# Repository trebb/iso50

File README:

ISO50 -- a 50% DIY computer keyboard

There are two variants of the ISO50 keyboard: hand-wired and
PCB-based.  Files and directories that have "pcb" in their name are
part of the PCB-based variant.

The hardware part is covered in directory ./hardware.

Firmware is based on TMK (https://github.com/tmk/tmk_keyboard); see
directories ./firmware or ./firmware-pcb, respectively.

http://imgur.com/a/XgsYZ
http://imgur.com/a/m9RCg

The name of this project refers to the standard 105-key ISO keyboard
layout, reduced to 50 %.  It is not related to anything using the
photography-related connotation of the name.  It is not affiliated
with http://blog.iso50.com/.

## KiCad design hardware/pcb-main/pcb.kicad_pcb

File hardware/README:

To build the keyboard, two laser-cut plates, an optional PCB, a
3D-printed frame, and a sticker that covers the screw heads and holes
on the bottom need to be made.

Files in this directory

- top-plate.dxf, bottom-plate.dxf, top-plate-pcb.dxf,
  bottom-plate-pcb.dxf

Files for laser cutting the plates.  Top should be 1.5 mm, bottom
1.0 mm (hand-wired) or 1.5 mm (PCB).

- top-plate-pcb-pcb.dxf

Helper file used for the KiCad project in ./pcb-top-plate/.

- frame.dxf, frame-pcb.dxf

Various shapes and parameters that are read by frame.scad or
frame-pcb.scad, respectively.  frame.dxf also contains a wiring
schema.

- frame.scad, frame-pcb.scad

Renders the (merely decorative) keyboard frame. 'make frame.stl' or
'make frame-pcb.stl' should create a 3D-printable .stl file.

- bottom-label-de.svg, bottom-label-pcb-de.svg

Legend image intended to be put onto the bottom of the keyboard.  'make
bottom-label-de.pdf' or 'make bottom-label-pcb-de.pdf' should create a
printable pdf that can be scaled to A4 size and printed on adhesive
film.

- foot-template.dxf

Template for cutting the bottom label, placing the adhesive feet, and
cutting an insulating layer that goes on top of the bottom plate.

- pcb-main/

KiCad project of the PCB.

- ./pcb-top-plate/, ./pcb-bottom-plate/

KiCad projects containing PCB-shaped alternatives to top-plate-pcb.dxf
and bottom-plate-dxf.

Software used

LibreCAD 2.08 (.dxf)
OpenSCAD 2015.03 (.stl)
Inkscape 0.9.1 (.svg)
KiCad r6904

Other parts:

- 52 Cherry-style switches

- 1 2u Costar stabilizer set

- USB cable: Mini for the hand-wiring, Micro for the PCB.

- An ISO keycap set that contains

  - 6 1.25u bottom row keys (most sets contain 7),

  - 7 1.5u bottom row keys (only a few keysets on the market contain
    that much), and

  - an asymmetrical, stepped CapsLock key

- 12 standoffs M2 x 6.3 mm (hand-wired) or M2 x 4.5 mm (PCB)

- 52 diodes 1N4148

- For the hand wiring:

  - Teensy 2.0

  - 3 LEDs, 3 resistors 330 Ohm

- For components of the PCB variant, consult the KiCad project in
  directory ./pcb-main.

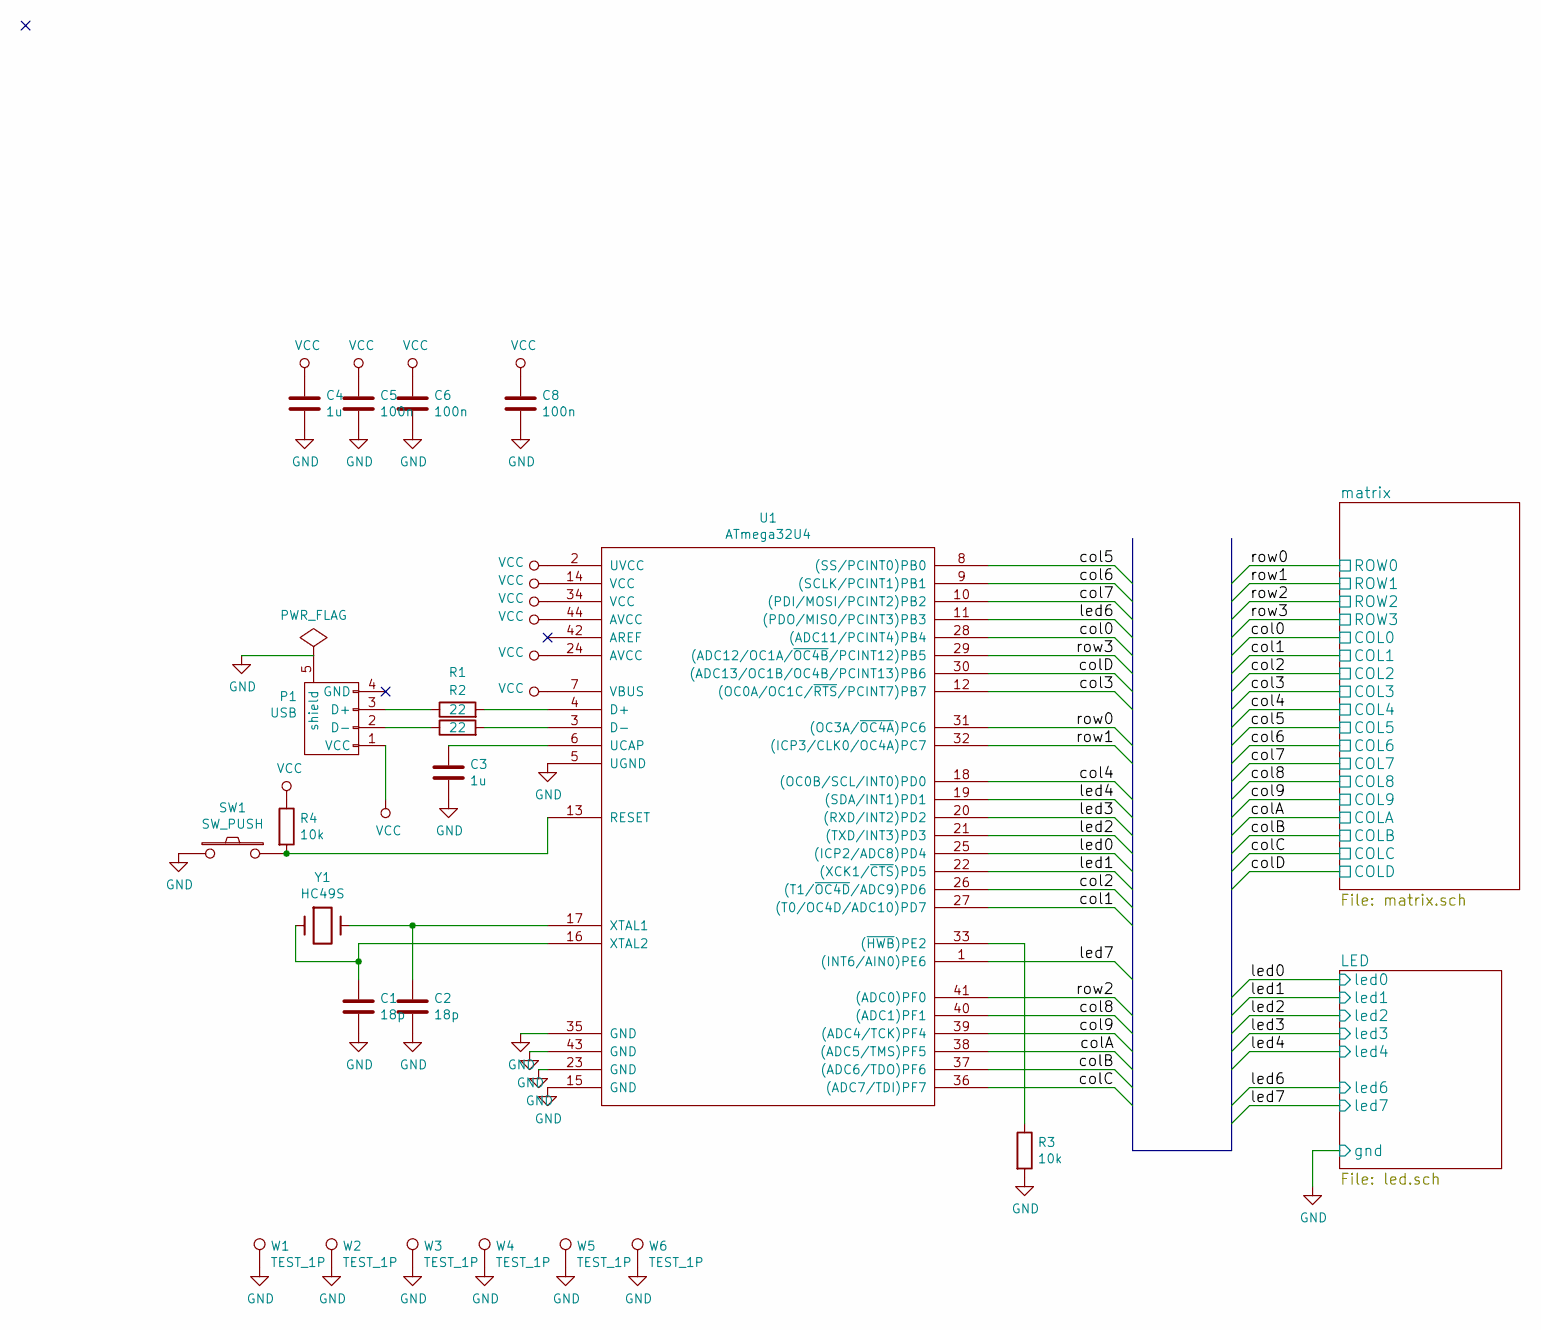
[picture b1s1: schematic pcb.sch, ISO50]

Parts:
C1, C2: 18p; C_1206_HandSoldering
C3, C4: 1u; C_1206_HandSoldering
C5, C6, C8: 100n; C_1206_HandSoldering
P1: USB; USB_Micro-207A-BBA0-R
R1, R2: 22; Resistor_Horizontal_RM7mm
R3, R4: 10k; Resistor_Horizontal_RM7mm
SW1: SW_PUSH; SW_PUSH_SMALL
U1: ATmega32U4; MLF-44_Atmel
W1, W2, W3, W4, W5, W6: TEST_1P; Spring-Contact_SMD
Y1: HC49S; Crystal_HC49-U_Vertical

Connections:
/col0: U1.28 ((ADC11/PCINT4)PB4); also elsewhere on the board
/col1: U1.27 ((T0/OC4D/ADC10)PD7); also elsewhere on the board
/col2: U1.26 ((T1/~OC4D~/ADC9)PD6); also elsewhere on the board
/col3: U1.12 ((OC0A/OC1C/~RTS~/PCINT7)PB7); also elsewhere on the board
/col4: U1.18 ((OC0B/SCL/INT0)PD0); also elsewhere on the board
/col5: U1.8 ((SS/PCINT0)PB0); also elsewhere on the board
/col6: U1.9 ((SCLK/PCINT1)PB1); also elsewhere on the board
/col7: U1.10 ((PDI/MOSI/PCINT2)PB2); also elsewhere on the board
/col8: U1.40 ((ADC1)PF1); also elsewhere on the board
/col9: U1.39 ((ADC4/TCK)PF4); also elsewhere on the board
/colA: U1.38 ((ADC5/TMS)PF5); also elsewhere on the board
/colB: U1.37 ((ADC6/TDO)PF6); also elsewhere on the board
/colC: U1.36 ((ADC7/TDI)PF7); also elsewhere on the board
/colD: U1.30 ((ADC13/OC1B/OC4B/PCINT13)PB6); also elsewhere on the board
/led0: U1.25 ((ICP2/ADC8)PD4); also elsewhere on the board
/led1: U1.22 ((XCK1/~CTS~)PD5); also elsewhere on the board
/led2: U1.21 ((TXD/INT3)PD3); also elsewhere on the board
/led3: U1.20 ((RXD/INT2)PD2); also elsewhere on the board
/led4: U1.19 ((SDA/INT1)PD1); also elsewhere on the board
/led6: U1.11 ((PDO/MISO/PCINT3)PB3); also elsewhere on the board
/led7: U1.1 ((INT6/AIN0)PE6); also elsewhere on the board
/row0: U1.31 ((OC3A/~OC4A~)PC6); also elsewhere on the board
/row1: U1.32 ((ICP3/CLK0/OC4A)PC7); also elsewhere on the board
/row2: U1.41 ((ADC0)PF0); also elsewhere on the board
/row3: U1.29 ((ADC12/OC1A/~OC4B~/PCINT12)PB5); also elsewhere on the board
GND: C1.2, C2.2, C3.2, C4.2, C5.2, C6.2, C8.2, P1.5 (shield), R3.2, SW1.2, U1.5 (UGND), U1.15 (GND), U1.23 (GND), U1.35 (GND), U1.43 (GND), W1.1, W2.1, W3.1, W4.1, W5.1, W6.1; also elsewhere on the board
unnamed: C1.1, U1.16 (XTAL2), Y1.1
unnamed: C2.1, U1.17 (XTAL1), Y1.2
unnamed: C3.1, U1.6 (UCAP)
unnamed: P1.2 (D-), R2.1
unnamed: P1.3 (D+), R1.1
unnamed: R1.2, U1.4 (D+)
unnamed: R2.2, U1.3 (D-)
unnamed: R3.1, U1.33 ((~HWB~)PE2)
unnamed: R4.2, SW1.1, U1.13 (RESET)
VCC: C4.1, C5.1, C6.1, C8.1, P1.1 (VCC), R4.1, U1.2 (UVCC), U1.7 (VBUS), U1.14 (VCC), U1.24 (AVCC), U1.34 (VCC), U1.44 (AVCC)

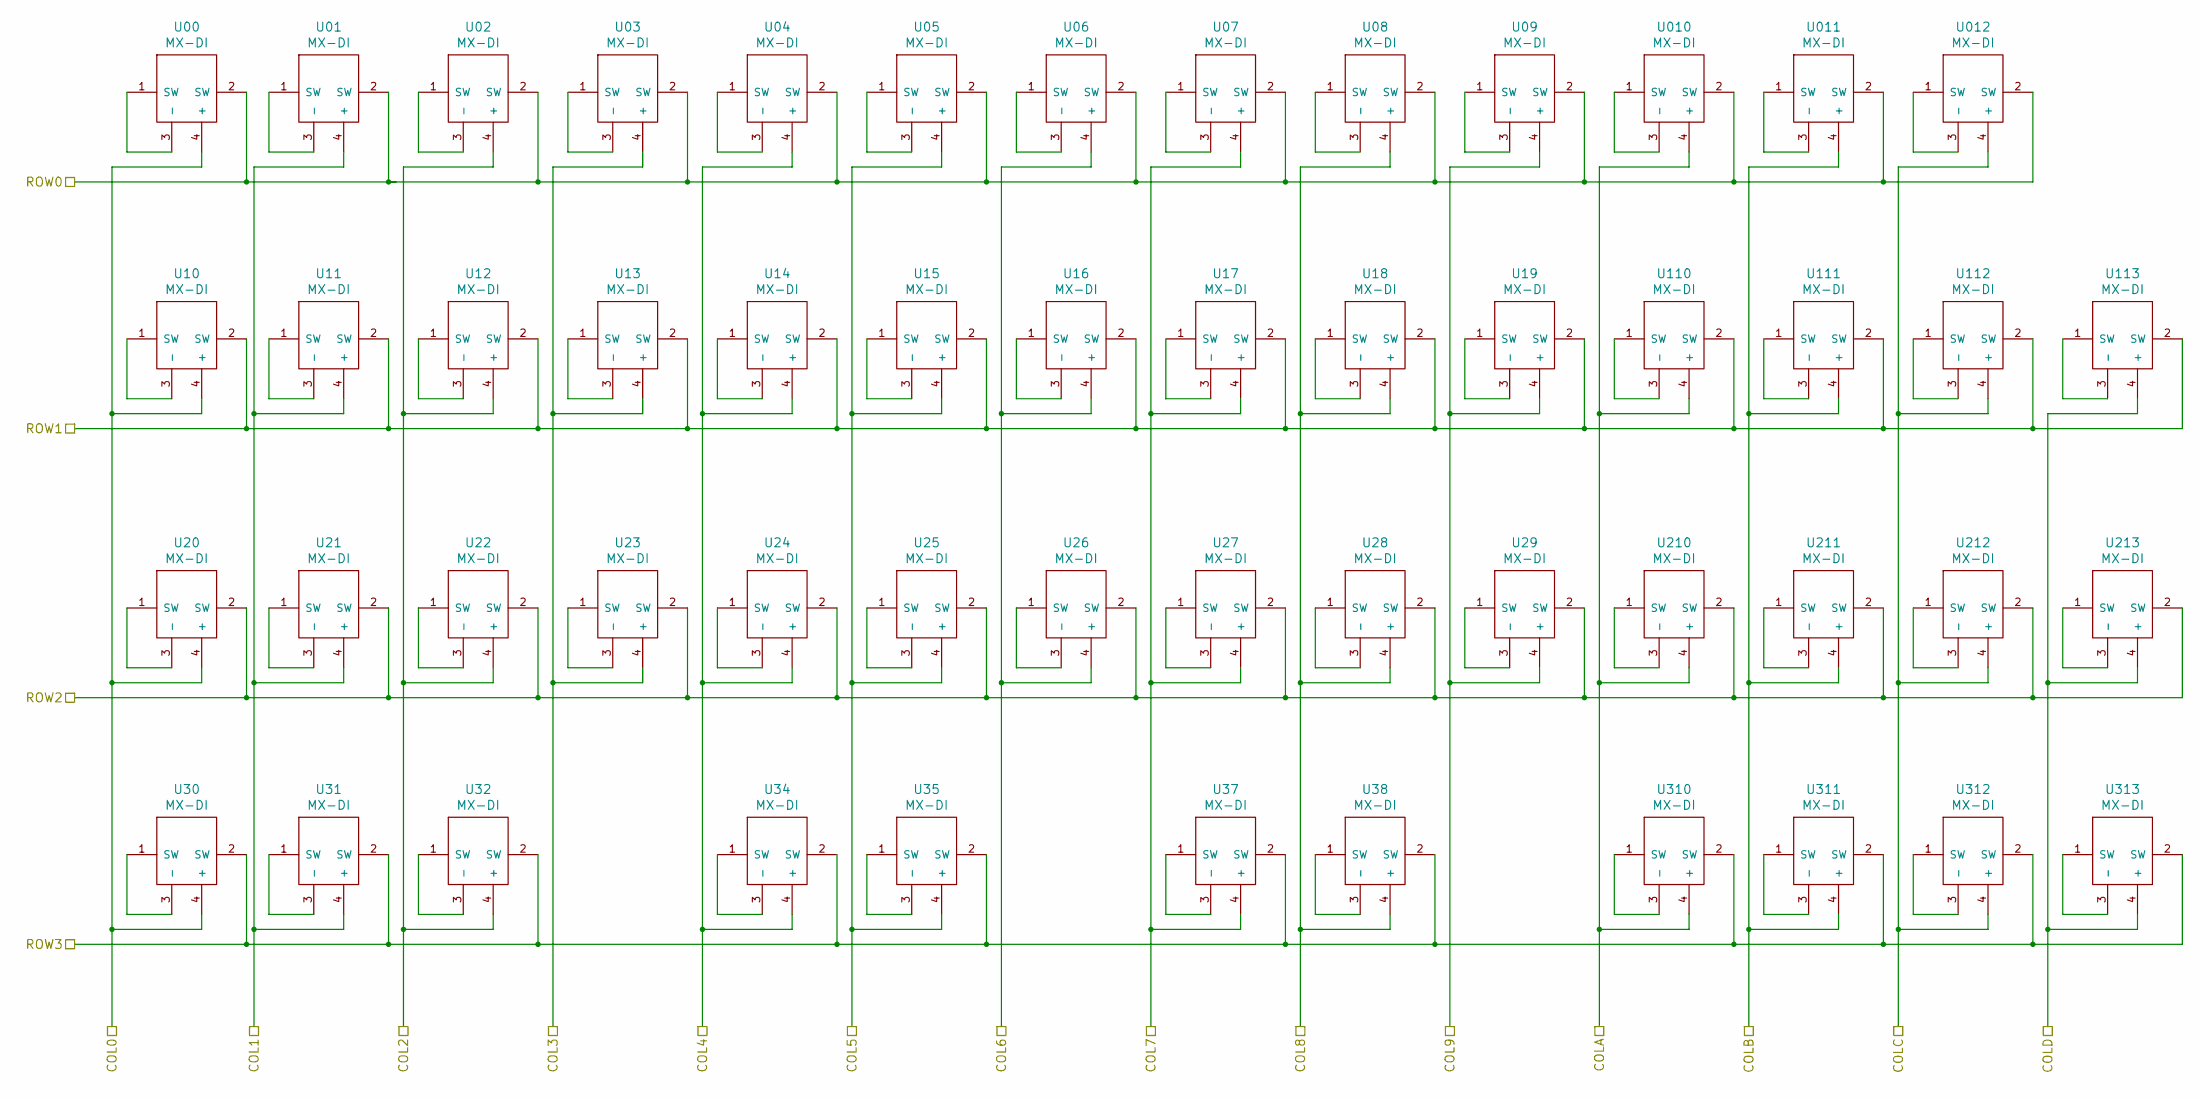
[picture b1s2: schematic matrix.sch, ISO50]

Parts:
U00, U01, U02, U03, U04, U05, U06, U07, U08, U09, U010, U10, U011, U11, U012, U12, U13, U14, U15, U16, U17, U18, U19, U20, U21, U22, U23, U24, U25, U26, U27, U28, U29, U30, U31, U32, U34, U35, U37, U38, U110, U111, U112, U113, U210, U211, U212, U213, U310, U311, U312, U313: MX-DI; MXDIODE

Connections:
/col0: U00.4 (+), U10.4 (+), U20.4 (+), U30.4 (+); also elsewhere on the board
/col1: U01.4 (+), U11.4 (+), U21.4 (+), U31.4 (+); also elsewhere on the board
/col2: U02.4 (+), U12.4 (+), U22.4 (+), U32.4 (+); also elsewhere on the board
/col3: U03.4 (+), U13.4 (+), U23.4 (+); also elsewhere on the board
/col4: U04.4 (+), U14.4 (+), U24.4 (+), U34.4 (+); also elsewhere on the board
/col5: U05.4 (+), U15.4 (+), U25.4 (+), U35.4 (+); also elsewhere on the board
/col6: U06.4 (+), U16.4 (+), U26.4 (+); also elsewhere on the board
/col7: U07.4 (+), U17.4 (+), U27.4 (+), U37.4 (+); also elsewhere on the board
/col8: U08.4 (+), U18.4 (+), U28.4 (+), U38.4 (+); also elsewhere on the board
/col9: U09.4 (+), U19.4 (+), U29.4 (+); also elsewhere on the board
/colA: U010.4 (+), U110.4 (+), U210.4 (+), U310.4 (+); also elsewhere on the board
/colB: U011.4 (+), U111.4 (+), U211.4 (+), U311.4 (+); also elsewhere on the board
/colC: U012.4 (+), U112.4 (+), U212.4 (+), U312.4 (+); also elsewhere on the board
/colD: U113.4 (+), U213.4 (+), U313.4 (+); also elsewhere on the board
/row0: U00.2 (SW), U01.2 (SW), U02.2 (SW), U03.2 (SW), U04.2 (SW), U05.2 (SW), U06.2 (SW), U07.2 (SW), U08.2 (SW), U09.2 (SW), U010.2 (SW), U011.2 (SW), U012.2 (SW); also elsewhere on the board
/row1: U10.2 (SW), U11.2 (SW), U12.2 (SW), U13.2 (SW), U14.2 (SW), U15.2 (SW), U16.2 (SW), U17.2 (SW), U18.2 (SW), U19.2 (SW), U110.2 (SW), U111.2 (SW), U112.2 (SW), U113.2 (SW); also elsewhere on the board
/row2: U20.2 (SW), U21.2 (SW), U22.2 (SW), U23.2 (SW), U24.2 (SW), U25.2 (SW), U26.2 (SW), U27.2 (SW), U28.2 (SW), U29.2 (SW), U210.2 (SW), U211.2 (SW), U212.2 (SW), U213.2 (SW); also elsewhere on the board
/row3: U30.2 (SW), U31.2 (SW), U32.2 (SW), U34.2 (SW), U35.2 (SW), U37.2 (SW), U38.2 (SW), U310.2 (SW), U311.2 (SW), U312.2 (SW), U313.2 (SW); also elsewhere on the board
unnamed: U00.1 (SW), U00.3 (-)
unnamed: U01.1 (SW), U01.3 (-)
unnamed: U02.1 (SW), U02.3 (-)
unnamed: U03.1 (SW), U03.3 (-)
unnamed: U04.1 (SW), U04.3 (-)
unnamed: U05.1 (SW), U05.3 (-)
unnamed: U06.1 (SW), U06.3 (-)
unnamed: U07.1 (SW), U07.3 (-)
unnamed: U08.1 (SW), U08.3 (-)
unnamed: U09.1 (SW), U09.3 (-)
unnamed: U10.1 (SW), U10.3 (-)
unnamed: U010.1 (SW), U010.3 (-)
unnamed: U11.1 (SW), U11.3 (-)
unnamed: U011.1 (SW), U011.3 (-)
unnamed: U12.1 (SW), U12.3 (-)
unnamed: U012.1 (SW), U012.3 (-)
unnamed: U13.1 (SW), U13.3 (-)
unnamed: U14.1 (SW), U14.3 (-)
unnamed: U15.1 (SW), U15.3 (-)
unnamed: U16.1 (SW), U16.3 (-)
unnamed: U17.1 (SW), U17.3 (-)
unnamed: U18.1 (SW), U18.3 (-)
unnamed: U19.1 (SW), U19.3 (-)
unnamed: U20.1 (SW), U20.3 (-)
unnamed: U21.1 (SW), U21.3 (-)
unnamed: U22.1 (SW), U22.3 (-)
unnamed: U23.1 (SW), U23.3 (-)
unnamed: U24.1 (SW), U24.3 (-)
unnamed: U25.1 (SW), U25.3 (-)
unnamed: U26.1 (SW), U26.3 (-)
unnamed: U27.1 (SW), U27.3 (-)
unnamed: U28.1 (SW), U28.3 (-)
unnamed: U29.1 (SW), U29.3 (-)
unnamed: U30.1 (SW), U30.3 (-)
unnamed: U31.1 (SW), U31.3 (-)
unnamed: U32.1 (SW), U32.3 (-)
unnamed: U34.1 (SW), U34.3 (-)
unnamed: U35.1 (SW), U35.3 (-)
unnamed: U37.1 (SW), U37.3 (-)
unnamed: U38.1 (SW), U38.3 (-)
unnamed: U110.1 (SW), U110.3 (-)
unnamed: U111.1 (SW), U111.3 (-)
unnamed: U112.1 (SW), U112.3 (-)
unnamed: U113.1 (SW), U113.3 (-)
unnamed: U210.1 (SW), U210.3 (-)
unnamed: U211.1 (SW), U211.3 (-)
unnamed: U212.1 (SW), U212.3 (-)
unnamed: U213.1 (SW), U213.3 (-)
unnamed: U310.1 (SW), U310.3 (-)
unnamed: U311.1 (SW), U311.3 (-)
unnamed: U312.1 (SW), U312.3 (-)
unnamed: U313.1 (SW), U313.3 (-)

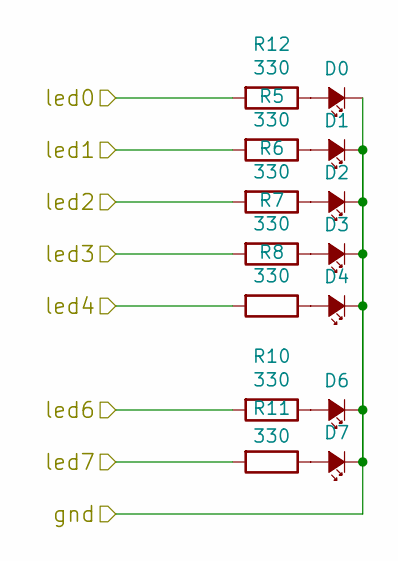
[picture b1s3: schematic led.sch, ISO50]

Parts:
D0, D1, D2, D3, D4, D6, D7: Led_Small; LED-3MM
R5, R6, R7, R8, R10, R11, R12: 330; Resistor_Horizontal_RM7mm

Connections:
/led0: R12.2; also elsewhere on the board
/led1: R5.2; also elsewhere on the board
/led2: R6.2; also elsewhere on the board
/led3: R7.2; also elsewhere on the board
/led4: R8.2; also elsewhere on the board
/led6: R10.2; also elsewhere on the board
/led7: R11.2; also elsewhere on the board
GND: D0.1 (K), D1.1 (K), D2.1 (K), D3.1 (K), D4.1 (K), D6.1 (K), D7.1 (K); also elsewhere on the board
unnamed: D0.2 (A), R12.1
unnamed: D1.2 (A), R5.1
unnamed: D2.2 (A), R6.1
unnamed: D3.2 (A), R7.1
unnamed: D4.2 (A), R8.1
unnamed: D6.2 (A), R10.1
unnamed: D7.2 (A), R11.1

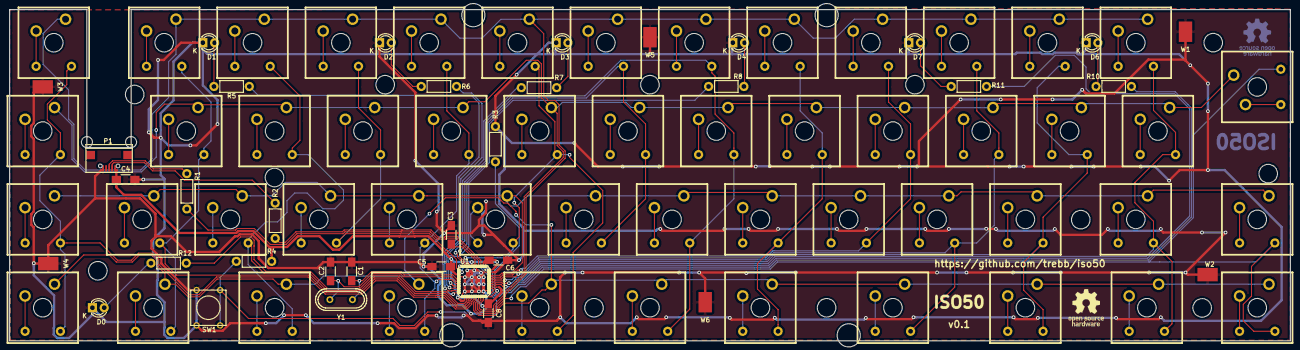
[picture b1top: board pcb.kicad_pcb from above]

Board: 2 copper layers, 276.2 x 71.4 mm, 87 parts (0 on the bottom side), 95 nets.

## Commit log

2016-07-30 Initial commit
    - Firmware compiles.
    - Completely untested.
2016-07-30 Add licence
2016-07-31 Fix a few obvious bugs in keymap
    (Still untested.)
2016-07-31 Adapt bottom label
2016-07-31 More .gitignore
2016-08-01 Initial design of a 3D-printable frame
2016-08-04 Add functionality and beauty to frame
    - Give it a more rounded shape.
    - Add a cable routing.
    - Add an "ISO50" imprint.
2016-08-04 Move hardware stuff into its own directory
2016-08-05 Draw an insulating layer
    It goes between switches and bottom plate.
2016-08-06 Add wiring plan
2016-08-07 Change a few symbols in bottom label
2016-08-07 Improve wiring plan
2016-08-07 Add ./hardware/README
2016-08-07 In ./hardware/: rename files, add Makefile
2016-08-07 Firmware: add/improve comments
2016-08-12 Reduce casing height by 0.7 mm
2016-08-13 Tweak bottom label
2016-08-13 Fix AltGr Layer
2016-08-14 Prune firmware build process
2016-08-14 Fix position of reset button on bottom label
2016-08-20 Wiring plan: position Teensy more realistically
2016-08-27 Add missing symbol in bottom label
2016-08-28 Add documentation
2016-09-02 Update READMEs
2016-09-04 Update README
    Add clarification what the project name is and is not about.
2016-09-20 Fix bugs in CAD files
    - Reduce size of stabilizer holes.
    - Replace polygons by arcs and circles.
    - Move the reset hole.
    - Move a standoff position whose screw head collided with the
    stabilizer wire.
2016-10-06 Add PCB
2016-10-06 Reduce PCB width
2016-10-06 Add steel top plate for PCB version
2016-10-09 Add plates for the PCB version
2016-10-15 Add PCB version of 3D-printed frame
2016-10-28 Add PCB version of the bottom label
2016-10-31 Add PCB firmware
2016-10-31 We have an official USB VID/PID combination
    Thanks to http://pid.codes.
2016-10-31 Update README and BUGS
2016-10-31 Fix typo in README
2016-10-31 .gitignore autosave files
2016-10-31 Edit PCB version of bottom label
2016-11-01 Update hardware/Makefile
2016-11-06 Add template for cutting bottom label and insulating layer
    (Belongs to the PCB version of the keyboard.)
2016-11-11 Remove an unnecessary hole from foot template
2016-11-20 Prepare Github-pages with a set of generated files
2016-11-20 gh-pages pseudo commit
2016-11-20 Fix Github-pages file set
